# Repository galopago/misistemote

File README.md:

# MISISTEMOTE

## VERSATILE, COMPACT AND ROBUST ELECTRONIC HARDWARE PROTOTYPING SYSTEM

Misistemote is an Open Source, modular ecosystem that uses pre-made PCB to mix and match your choice of processor board. Is oriented to make small, mobile, battery powered electronic projects work in real conditions in a very short time.

Read this in other languages: [Español](/assets/markdown/README.es.md)

The ecosystem follows 3 simple rules:

* PCB: pre-made, simple and easy to replicate prototyping boards
* Enclosure: Generic, waterproof, low cost, easily available.
* Cable entry: Cable glands for external sensors or power

## PCB DESIGN

The PCB design followed one simple principle: Try to place the MCU board as close as possible to a corner, maximizing the contiguous available PCB remaining space.

Small microcontroller         |Medium MCU                      | Big MCU                 
------------------------------|--------------------------------|-----------------------------
      |      | 
 | |

Female headers could be added to make MCU module reusable, and to gain some space below. Notice battery socket placed in available space!

MCU plugged                      |Free space below                | Free space side view                 
---------------------------------|--------------------------------|------------------------------
 | | 

Connecting wires on the underside

## WATERPROOF ENCLOSURE

The best enclosures suited for the system are the ones that have external mount points and doesn't need to be opened to be fixed/detached.

Generic enclosure                    |Sports style enclosure              
-------------------------------------|------------------------------------
    |    
 | 

Depending of the enclosure used there are two methods for PCB fixation: Self tapping screws or flexible foam.

Screw fixing                      |Flexible foam fixing               
----------------------------------|------------------------------------
 |    
 | 

## CABLE ENTRY

If the project needs an external wired sensor or power cord, a cable gland should be used to stop exterior impurities from cause any damage to internal components. They also offer strain relief for the internal connections.

Big enclosure, thick cable       |Small enclosure, thin cable
------------------------------------|------------------------------------
  |    
 | 

## CABLE ENTRY - ALTERNATIVE METHOD

USB C connector for panel mount, provides power and USB 2.0 data signals. Use drilling helper found here [Panel mount drilling helper](https://github.com/galopago/panel-mount-drill-layouts)

.                                |.
---------------------------------|------------------------------------
 |    
 | 

## SAMPLE PROJECT

Temperature sensor based on ESP32 board with DS18B20 OneWire sensor, powered by a 3.2V 600mA LiFePo4 Battery. Waterproof, dustproof and wall mountable.

.                                |.
---------------------------------|------------------------------------
 |    
 | 

## Versions

There are several board versions, each one with different personalities

| HINT            | ENCLOSURE SIZE        | LINK                                     
|-----------------|-----------------------|---------------------------------------------------
| Many MCU boards | 83x58mm               | [mcu-proto-83x58mm](/mcu-proto-83x58mm)  
| Many MCU boards | 100x68mm "sonoff"     | [mcu-proto-100x68mm](/mcu-proto-100x68mm)  
| Many MCU boards | Sports Cam compatible | [mcu-proto-sportcam](/mcu-proto-sportcam)  
| ESP32-Cam       | 83x58mm               | [esp32cam-proto-83x58mm](/esp32cam-proto-83x58mm)  
| ESP32-Cam       | Sports Cam compatible | [esp32cam-proto-sportcam](/esp32cam-proto-sportcam)

Misistemote is an open source project by [Galopago](https://galopago.github.io/)

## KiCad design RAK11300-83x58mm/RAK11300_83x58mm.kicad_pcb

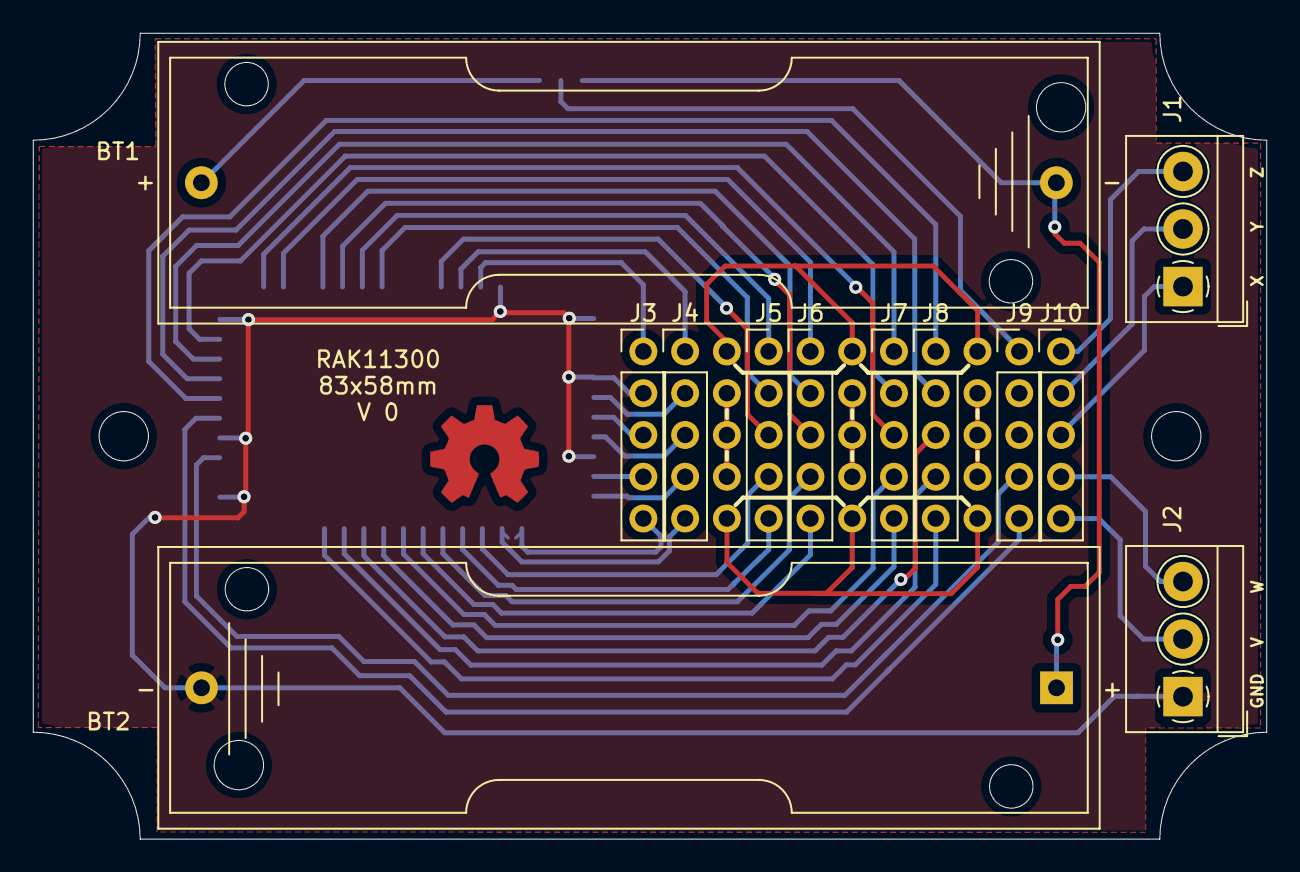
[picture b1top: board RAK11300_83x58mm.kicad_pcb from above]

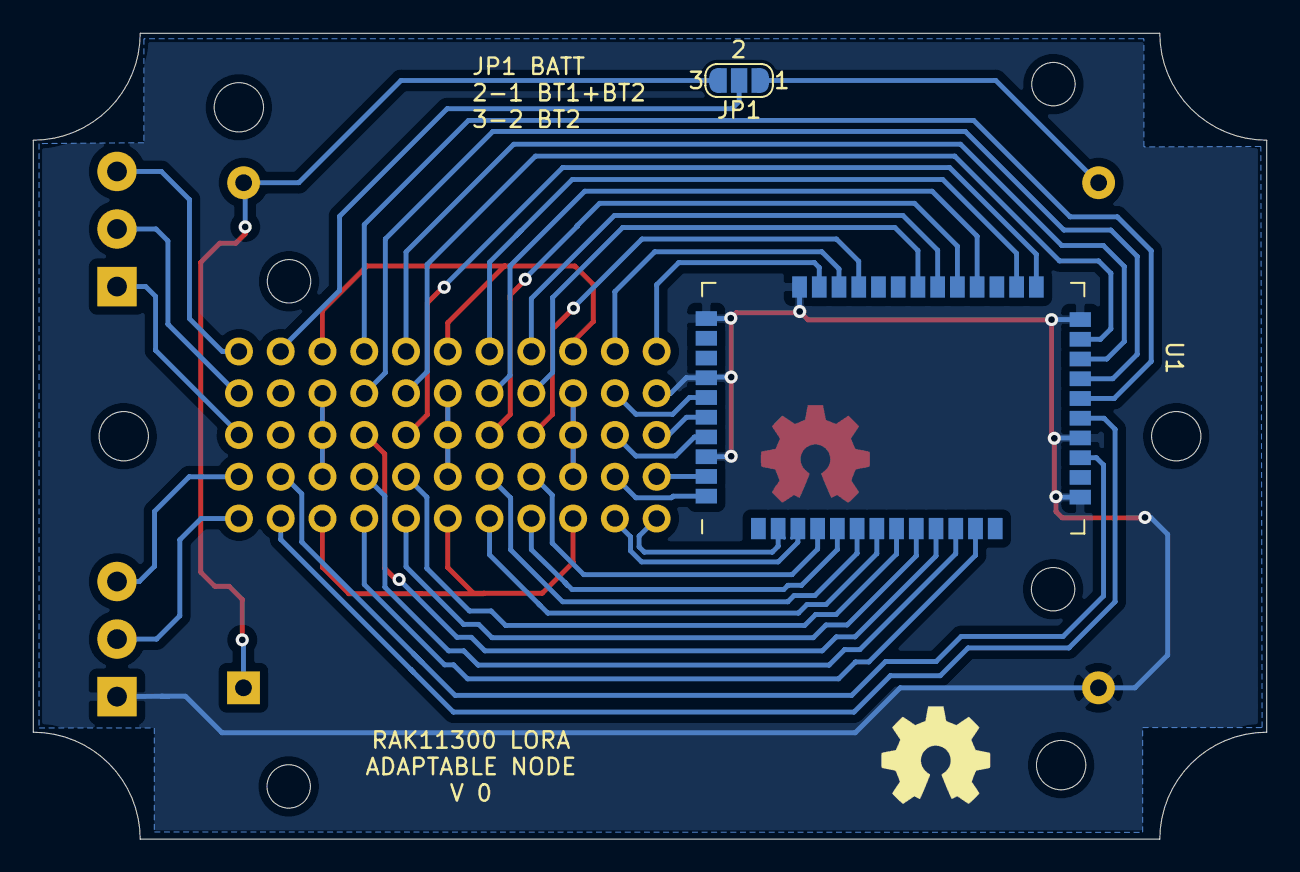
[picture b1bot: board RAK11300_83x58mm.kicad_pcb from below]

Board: 2 copper layers, 75.0 x 49.0 mm, 18 parts (2 on the bottom side), 40 nets.

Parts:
BT1, BT2: Battery_Cell; BatteryHolder_Keystone_2460_1xAA
H2, H3, H4, H5: MountingHole; MountingHole_3mm
J1, J2: Screw_Terminal_01x03; TerminalBlock_4Ucon_1x03_P3.50mm_Horizontal
J3, J4, J5, J6, J7, J8, J9, J10: Conn_01x05_Male; PinHeader_1x05_P2.54mm_Vertical
JP1: SolderJumper_3_Open; SolderJumper-3_P1.3mm_Open_RoundedPad1.0x1.5mm_NumberLabels
U1: RAK11300

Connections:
/P1J3: J3.1, U1.35
/P1J4: J4.1, U1.34
/P1J5: J5.1, U1.29
/P1J6: J6.1, U1.25
/P1J7: J7.1, U1.21
/P1J8: J8.1, U1.19
/P1J9: J9.1, JP1.2
/P1J10: J1.3, J10.1
/P2J4: J4.2, U1.41
/P2J5: J5.2, U1.30
/P2J6: J6.2, U1.27
/P2J7: J7.2, U1.22
/P2J8: J8.2, U1.20
/P2J10: J1.2, J10.2
/P3J3: J3.3, U1.42
/P3J4: J4.3, U1.43
/P3J5: J5.3, U1.33
/P3J6: J6.3, U1.28
/P3J7: J7.3, U1.24
/P3J8: J8.3, U1.10
/P3J10: J1.1, J10.3
/P4J3: J3.4, U1.45
/P4J4: J4.4, U1.46
/P4J5: J5.4, U1.4
/P4J6: J6.4, U1.6
/P4J7: J7.4, U1.8
/P4J8: J8.4, U1.11
/P4J9: J9.4, U1.16
/P4J10: J2.3, J10.4
/P5J5: J5.5, U1.5
/P5J6: J6.5, U1.7
/P5J7: J7.5, U1.9
/P5J8: J8.5, U1.12
/P5J9: J9.5, U1.18
/P5J10: J2.2, J10.5
/USB_N: J3.5, U1.2
/USB_P: J4.5, U1.3
GND: BT2.2, J2.1, J3.2, U1.14, U1.17, U1.23, U1.36, U1.37, U1.40, U1.44
unnamed: BT1.1, JP1.1
unnamed: BT1.2, BT2.1, JP1.3

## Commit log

2022-02-08 added RAK11300 83x58mm
2022-02-09 renamed folder
2022-02-09 proto mcu project added
2022-02-09 added gerbers
2022-02-09 added gerbers panel
2022-02-09 esp32cam gerbers
2022-02-09 esp32cam sportcam gerbers
2022-02-10 initial shape
2022-02-10 pads in process
2022-02-10 adjusted drill distance
2022-02-10 all pads placed
2022-02-11 some silks added
2022-02-11 all silks finished
2022-02-11 single gerbers
2022-02-15 added pinout
2022-02-15 started readme
2022-02-15 started readme+
2022-02-15 added missing trace
2022-02-15 single gerber
2022-02-15 panel gerber
2022-02-15 measurements started
2022-02-15 added rpi zero compat started
2022-02-16 pi zero added single gerber
2022-02-16 gerbers sinlge corrected
2022-02-16 +0.5mm shift
2022-02-16 gerbers +0.5mm shift
2022-02-16 gerbers panel +0.5mm shift
2022-02-16 gerbers panel +0.5mm shift renamed
2022-02-17 improved connector place
2022-02-17 pinout
2022-02-17 pinout-deleted svg
2022-02-18 doc:(ESP32CAM_PROTO_SPORTCAM)pinout and trace pattern
2022-02-19 doc:(ESP32CAM_PROTO_83x58)pinout and trace pattern
2022-02-20 doc:(ESP32CAM_PROTO_SPORTCAM)started readme
2022-02-20 doc:(ESP32CAM_PROTO_SPORTCAM)image link fix
2022-02-20 doc:(ESP32CAM_PROTO_SPORTCAM)pinout rotated
2022-02-20 doc:(ESP32CAM_PROTO_SPORTCAM)pinout text
2022-02-20 doc:(ESP32CAM_PROTO_SPORTCAM)vertical and horizontal
2022-02-20 doc:(ESP32CAM_PROTO_SPORTCAM)vertical without SD
2022-02-20 doc:(ESP32CAM_PROTO_SPORTCAM)sensor placed
2022-02-20 doc:(ESP32CAM_PROTO_SPORTCAM)free space
2022-02-20 doc:(ESP32CAM_PROTO_SPORTCAM)how to use repo
2022-02-20 doc:(ESP32CAM_PROTO_SPORTCAM)titles added
2022-02-20 doc:(ESP32CAM_PROTO_SPORTCAM)pics improved
2022-02-20 doc:(ESP32CAM_PROTO_SPORTCAM)spelling check
2022-02-20 doc:(ESP32CAM_PROTO_83x59)started readme
2022-02-20 doc:(ESP32CAM_PROTO_83x59)horizontal&vertical
2022-02-20 doc:(ESP32CAM_PROTO_83x59)all images
2022-02-20 doc:(ESP32CAM_PROTO_83x59)text modif
2022-02-20 doc:(ESP32CAM_PROTO_83x59)rak11300 started readme
2022-02-20 doc:(ESP32CAM_PROTO_83x59)initial pics
2022-02-20 doc:(ESP32CAM_PROTO_83x59)all pics
2022-02-20 doc:(MCU_PROTO_100x68)all pics
2022-02-20 doc:(MCU_PROTO_83x58)all pics
2022-02-21 doc:(RAK11300_83x58)pdf+started readme
2022-02-21 doc:(RAK11300_83x58)text adjustments
2022-02-21 doc:(RAK11300_83x58)text cheked
2022-02-21 doc:(MCU_PROTO_83x58)readme started
2022-02-21 doc:(MCU_PROTO_83x58)readme finished text
2022-02-21 doc:(MCU_PROTO_83x58)dil pics
2022-02-21 doc:(MCU_PROTO_83x58)dil text
2022-02-22 doc:(MCU_PROTO_83x58)dil text add
2022-02-22 doc:(MCU_PROTO_83x58)text corrected
2022-02-22 doc:(MCU_PROTO_83x58)text corrected comma
2022-02-22 doc:(MCU_PROTO_100x68)readme started
2022-02-22 doc:(MCU_PROTO_100x68)space pic
2022-02-22 doc:(MCU_PROTO_100x68)panel removed
2022-02-22 doc:(TUSISTEMOTE ROOT)readme started
2022-02-23 doc:(TUSISTEMOTE ROOT)readme first words
2022-02-23 doc:(TUSISTEMOTE ROOT)readme first more text
2022-02-23 doc:(TUSISTEMOTE ROOT)initial pics
2022-02-23 doc:(TUSISTEMOTE ROOT)more pics
2022-02-23 doc:(TUSISTEMOTE ROOT)table pics
2022-02-23 doc:(TUSISTEMOTE ROOT)img type error
2022-02-23 doc:(TUSISTEMOTE ROOT)table space
2022-02-23 doc:(TUSISTEMOTE ROOT)mcu socket
2022-02-23 doc:(TUSISTEMOTE ROOT)mcu socket side
2022-02-23 doc:(TUSISTEMOTE ROOT)table fix
2022-02-23 doc:(TUSISTEMOTE ROOT)table fix?
2022-02-23 doc:(TUSISTEMOTE ROOT)fixing table!
2022-02-23 doc:(TUSISTEMOTE ROOT)deleted table
2022-02-23 doc:(TUSISTEMOTE ROOT)connections
2022-02-23 doc:(TUSISTEMOTE ROOT)connections typo
2022-02-23 doc:(TUSISTEMOTE ROOT)updated pics
2022-02-23 doc:(TUSISTEMOTE ROOT)mount pics
2022-02-23 doc:(TUSISTEMOTE ROOT)mount pics typo
2022-02-24 doc:(TUSISTEMOTE ROOT)screw pics
2022-02-24 doc:(TUSISTEMOTE ROOT)screw more pics
2022-02-24 doc:(TUSISTEMOTE ROOT)screw more pics typo
2022-02-24 doc:(TUSISTEMOTE ROOT)cable gland pics
2022-02-24 doc:(TUSISTEMOTE ROOT)cable gland pics more
2022-02-24 doc:(TUSISTEMOTE ROOT)pics sample proj
2022-02-24 doc:(TUSISTEMOTE ROOT)board versions
2022-02-24 doc:(TUSISTEMOTE ROOT)board versions fix
2022-03-03 doc:(TUSISTEMOTE ROOT)updated readme pics
2022-03-03 doc:(TUSISTEMOTE ROOT)readme typos
2022-03-03 doc:(TUSISTEMOTE ROOT)readme typos+
2022-03-03 doc:(TUSISTEMOTE ROOT)readme typos++
2022-03-03 doc:(TUSISTEMOTE ROOT)readme ES started
2022-03-03 doc:(TUSISTEMOTE ROOT)readme ES started+
2022-03-03 doc:(TUSISTEMOTE ROOT)readme ES started++
2022-03-04 doc:(TUSISTEMOTE ROOT)readme ES finished
2022-03-04 doc:(TUSISTEMOTE ROOT)readme ES correcting
2022-03-04 doc:(TUSISTEMOTE ROOT)readme ES checked
2022-03-07 doc:(TUSISTEMOTE ROOT)header title
2022-03-07 doc:(TUSISTEMOTE ROOT)header title fix
2022-03-11 doc:(tusistemote ROOT)renamed repo,folder changed links
2022-03-15 doc:(tusistemote root)license
2022-03-15 doc:(tusistemote mcu-proto-83x58mm)pcb enclosure img
2022-03-15 doc:(tusistemote mcu-proto-83x58mm)dil img
2022-03-15 doc:(tusistemote mcu-proto-83x58mm)small img
2022-03-15 doc:(tusistemote mcu-proto-83x58mm)big img
2022-03-15 doc:(tusistemote mcu-proto-83x58mm)double img
2022-03-15 doc:(tusistemote mcu-proto-100x68mm)enclosure img
2022-03-15 doc:(tusistemote mcu-proto-100x68mm)dil img
2022-03-15 doc:(tusistemote mcu-proto-100x68mm)small img
2022-03-15 doc:(tusistemote mcu-proto-100x68mm)big img
2022-03-15 doc:(tusistemote mcu-proto-100x68mm)doublerow img
2022-03-15 doc:(tusistemote mcu-proto-100x68mm)doublerow img+
2022-03-15 doc:(tusistemote mcu-proto-100x68mm)doublerow img++
2022-03-15 doc:(tusistemote mcu-proto-100x68mm)doublerow img+++
2022-03-15 doc:(tusistemote mcu-proto-100x68mm)old img del
2022-03-15 doc:(tusistemote mcu-proto-83x58mm)double text
2022-03-15 doc:(tusistemote mcu-proto-83x58mm)double text typo
2022-03-15 doc:(tusistemote mcu-proto-83x58mm)del old img
2022-03-15 doc:(tusistemote root)added sonoff enclosure link
2022-03-15 doc:(tusistemote root)dil space pics
2022-03-15 doc:(tusistemote root)dileted old img
2022-04-06 doc:(misistemote)changed name
2022-04-08 pcb:(misistemote 100x68)added holes pcb gerber
2022-06-03 deleted old folder
2022-06-07 updated pic
2022-06-07 updated svg
2022-06-07 updated small module
2022-06-07 updated dil uc pic
2022-06-08 updated uc big pic
2022-06-08 updated doublerow pic
2022-06-08 updated space down pic
2022-06-09 updated compatibility box pic
2022-06-09 updated compatibility text
2022-06-09 typo
2022-06-09 spell checked +
2022-06-09 updated pic compat box
2022-07-19 esp32 cam front cover
2022-07-19 esp32 cam back cover
2022-07-24 started mcu proto sportcam
2022-07-24 mcu proto sportcam deleted previous items
2022-07-24 mcu proto sportcam deleted previous tracks
2022-07-24 mcu proto sportcam mvp ready!
2022-07-25 mcu proto sportcam single gerber
2022-07-25 mcu proto sportcam gerber panel
2022-08-22 stared mcu sportscam
2022-08-22 stared mcu sportscam+
2022-08-22 stared mcu sportscam++
2022-08-22 stared mcu sportscam+++
2022-08-22 stared mcu sportscam++++
2022-08-22 stared mcu sportscam+++++
2022-08-22 stared mcu sportscam++++++
2022-08-22 stared mcu sportscam+++++++
2022-08-22 master readme added sportscam mcu
2022-08-22 master ES readme added sportscam mcu
2022-11-29 added usb panel pics
2022-11-30 added logo
2023-02-16 testing pt version
2023-02-16 testing pt version+
2023-02-16 testing pt version++
2023-02-16 testing pt version+++
2023-02-16 testing pt version++++
2023-02-16 testing pt version+++++
2023-02-17 started es test
2023-02-17 started es test+
2023-02-17 started es test++
2023-02-17 started es test+++
2023-02-17 started es test++++
2023-02-17 started es test+++++
2023-02-26 added link to Galopago
2025-10-15 Add new MCU proto board design for 115x70mm enclosure
    - Added complete KiCad project files for mcu-proto-115x70mm
    - Includes PCB design, schematic, and project configuration
    - Added custom library with RoundPad footprint (1.7mm pad, 1.0mm hole)
    - Included multiple backup versions from development process
    - New board size expands misistemote ecosystem compatibility
2025-10-15 Board routed with mounting holes and silkscreens ready
    - Completed PCB routing for mcu-proto-115x70mm
    - Added mounting holes for secure enclosure attachment
    - Implemented silkscreen layer with component labels and markings
    - Generated Gerber files and SVG previews for manufacturing
    - Added PadLink footprint for enhanced connectivity
    - Updated symbol library and footprint definitions
2025-10-16 Silkscreen on both sides and descriptive text. Generating gerbers for single board
    - Added silkscreen layer on both front and back sides of PCB
    - Implemented descriptive text and component labels on both faces
    - Generated complete Gerber files for single board manufacturing
    - Included copper layers (F_Cu, B_Cu), mask layers (F_Mask, B_Mask)
    - Added silkscreen layers (F_Silkscreen, B_Silkscreen) for both sides
    - Generated drill files (PTH.drl, NPTH.drl) for hole drilling
2025-11-07 Update to newer KiCad version and begin self-explanatory PCB improvements
2025-11-07 Minor revision update
2025-11-07 Silkscreen on front side
2025-11-08 Silks in back plate
2025-11-10 Created gerber files for single board
2025-11-10 Update backup files: remove old backup and add new backups
2025-11-24 Update MCU_PROTO_83x58mm: PCB improvements and Gerber file regeneration
    - Updated main PCB file (MCU_PROTO_83x58mm.kicad_pcb) with design improvements
    - Regenerated all Gerber files for single board (copper, mask, silkscreen, drills)
    - Updated panel Gerber files with new naming convention
    - Replaced old silkscreen files (B_SilkS/F_SilkS) with new Silkscreen versions
    - Removed obsolete SVG visualization files
    - Added new KiCad project files (.kicad_prl, .kicad_pro, .kicad_sch)
2025-11-24 Add backup files for MCU_PROTO_100x68mm
    - Added backup from November 10, 2025 (23:29)
    - Added backup from November 24, 2025 (09:57)
2026-01-07 Add universal proto PCB for 90x60mm enclosure
    - Created new mcu-proto-90x60mm project with KiCad files
    - Added Gerber files and library components
    - Included auto-backups from other projects (115x70mm and 83x58mm)
2026-01-07 Add Gerber files for single PCB (90x60mm)
2026-01-07 Add panel Gerber files for 90x60mm PCB
